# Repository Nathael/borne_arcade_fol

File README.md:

borne_arcade_fol
================

Borne Arcade pour la Fabrique d'Objets Libres

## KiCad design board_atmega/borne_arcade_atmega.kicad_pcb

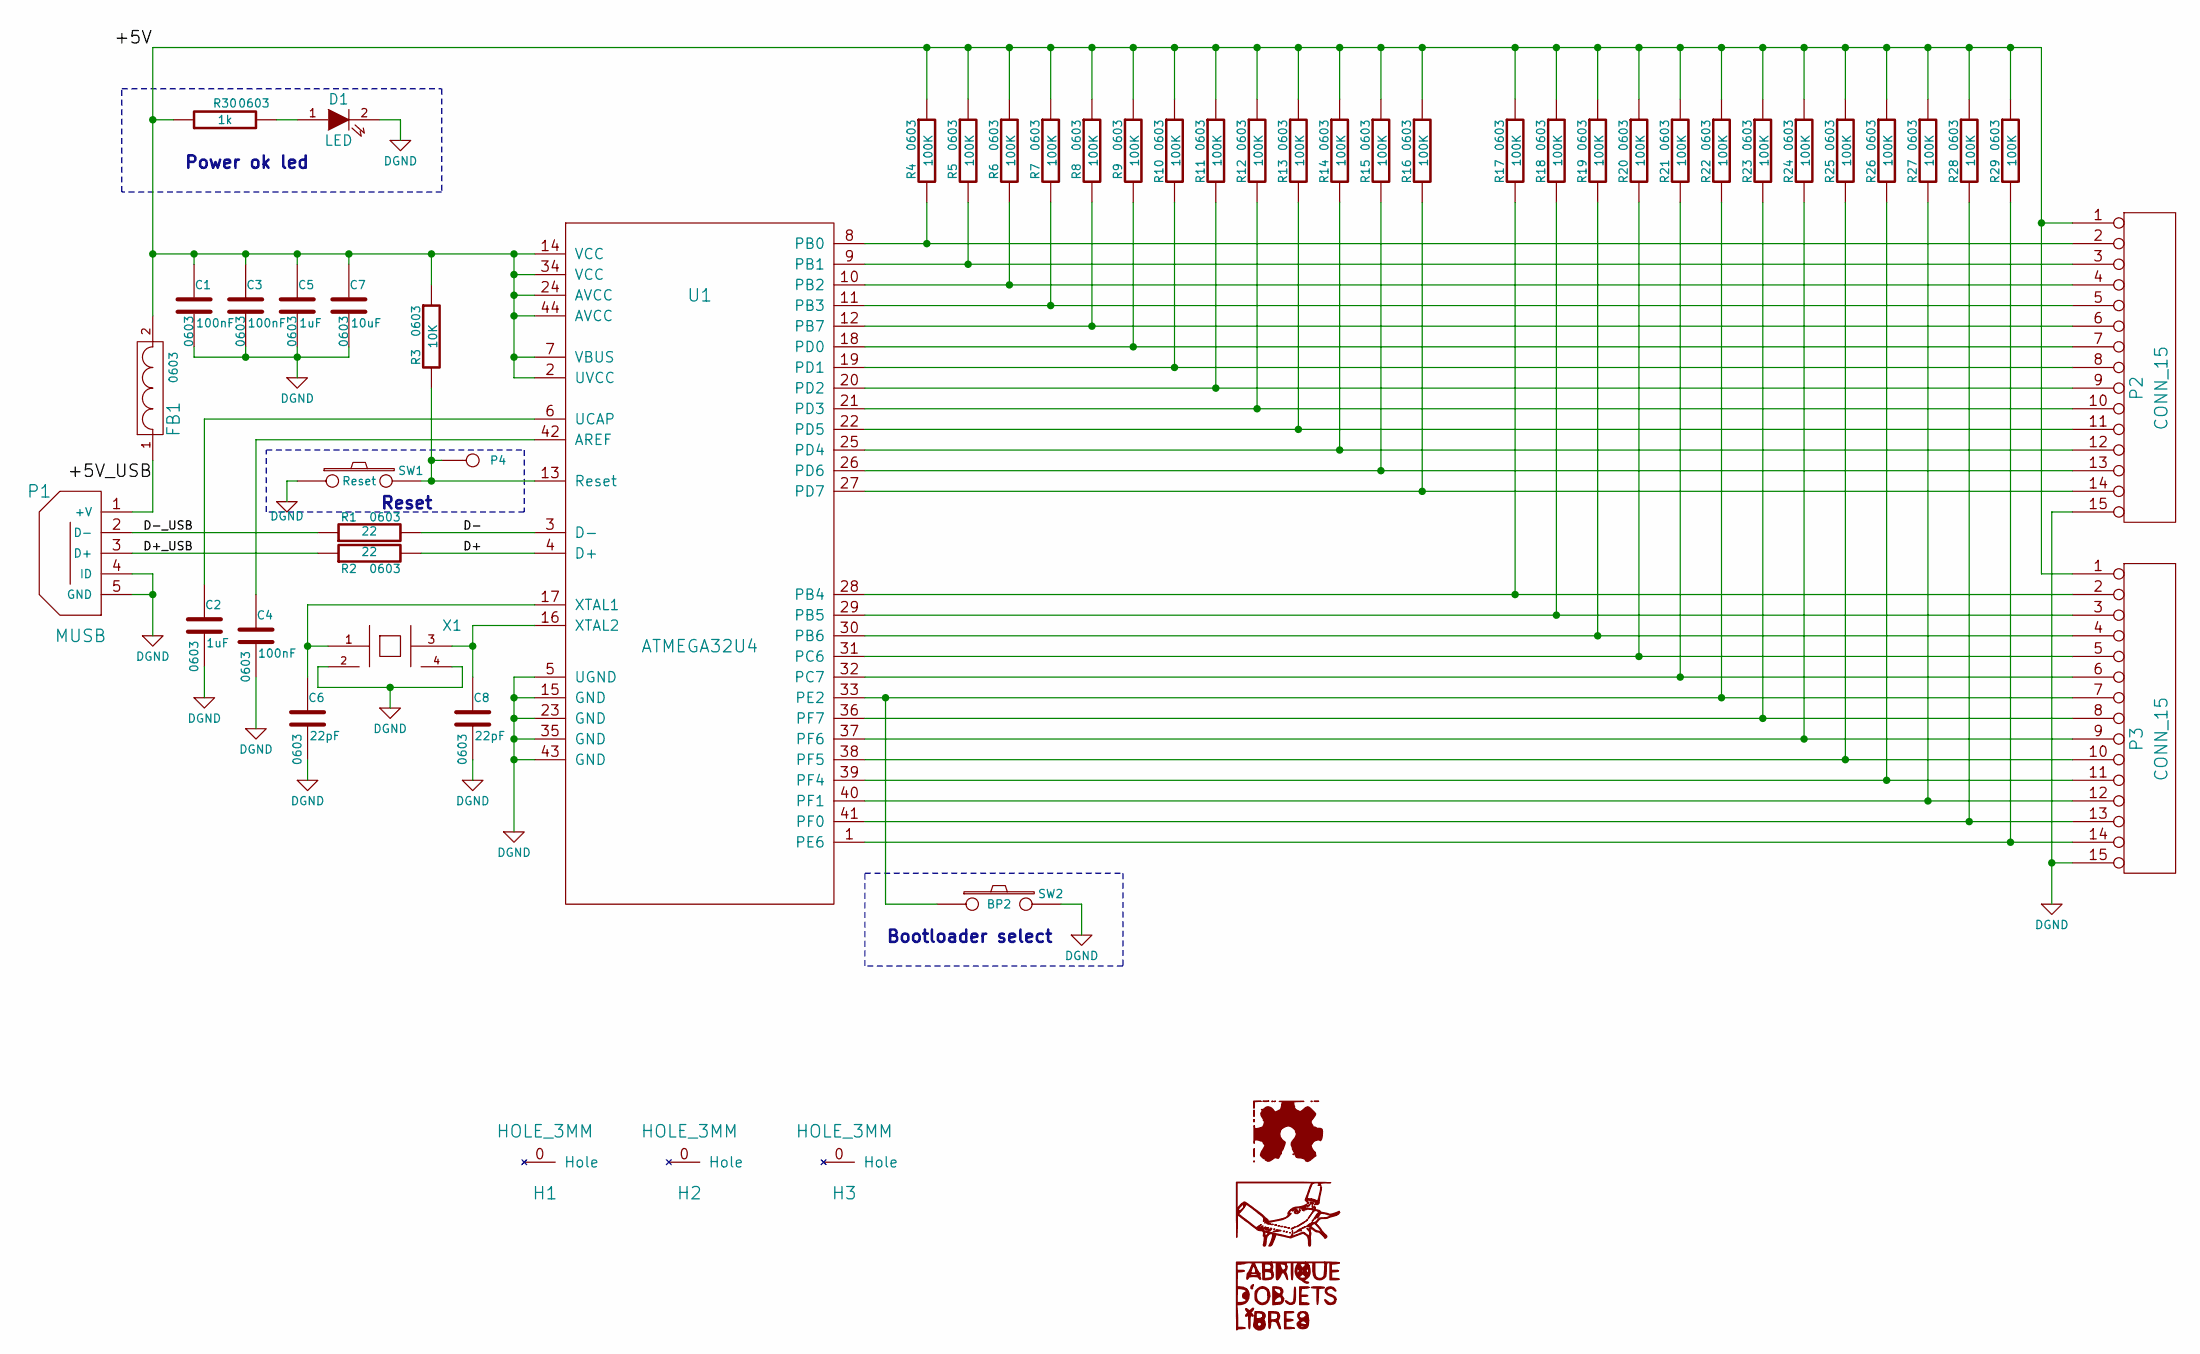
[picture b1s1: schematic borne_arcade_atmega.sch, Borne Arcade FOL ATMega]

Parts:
C1, C3, C4: 100nF; 0603
C2, C5: 1uF; 0603
C6, C8: 22pF; 0603
C7: 10uF; 0603
D1: LED
FB1: FILTER; 0603
G1: LOGO
G2: LOGO_FOL
G3: LOGO_OSHW
H1, H2, H3: HOLE_3MM
P1: MUSB
P2, P3: CONN_15
P4: CONN_1
R1, R2: 22; 0603
R3: 10K; 0603
R4, R5, R6, R7, R8, R9, R10, R11, R12, R13, R14, R15, R16, R17, R18, R19, R20, R21, R22, R23, R24, R25, R26, R27, R28, R29: 100K; 0603
R30: 1k; 0603
SW1: Reset
SW2: BP2
U1: ATMEGA32U4
X1: QUARTZ_CMS_4

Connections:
/+5V: C1.1, C3.1, C5.1, C7.1, FB1.2, P2.1, P3.1, R3.1, R4.1, R5.1, R6.1, R7.1, R8.1, R9.1, R10.1, R11.1, R12.1, R13.1, R14.1, R15.1, R16.1, R17.1, R18.1, R19.1, R20.1, R21.1, R22.1, R23.1, R24.1, R25.1, R26.1, R27.1, R28.1, R29.1, R30.1, U1.2 (UVCC), U1.7 (VBUS), U1.14 (VCC), U1.24 (AVCC), U1.34 (VCC), U1.44 (AVCC)
/+5V_USB: FB1.1, P1.1 (+V)
/D+: R2.2, U1.4 (D+)
/D+_USB: P1.3 (D+), R2.1
/D-: R1.2, U1.3 (D-)
/D-_USB: P1.2 (D-), R1.1
DGND: C1.2, C2.2, C3.2, C4.2, C5.2, C6.2, C7.2, C8.2, D1.2 (K), P1.4 (ID), P1.5 (GND), P2.15, P3.15, SW1.1, SW2.2, U1.5 (UGND), U1.15 (GND), U1.23 (GND), U1.35 (GND), U1.43 (GND), X1.2 (GND), X1.4 (GND)
unnamed: P2.9, R11.2, U1.20 (PD2)
unnamed: P2.8, R10.2, U1.19 (PD1)
unnamed: P2.7, R9.2, U1.18 (PD0)
unnamed: P2.6, R8.2, U1.12 (PB7)
unnamed: P2.5, R7.2, U1.11 (PB3)
unnamed: P2.4, R6.2, U1.10 (PB2)
unnamed: P2.3, R5.2, U1.9 (PB1)
unnamed: P2.2, R4.2, U1.8 (PB0)
unnamed: C2.1, U1.6 (UCAP)
unnamed: C8.1, U1.16 (XTAL2), X1.3
unnamed: P2.10, R12.2, U1.21 (PD3)
unnamed: P3.14, R29.2, U1.1 (PE6)
unnamed: D1.1 (A), R30.2
unnamed: P4.1, R3.2, SW1.2, U1.13 (Reset)
unnamed: P2.11, R13.2, U1.22 (PD5)
unnamed: P2.14, R16.2, U1.27 (PD7)
unnamed: P2.13, R15.2, U1.26 (PD6)
unnamed: P2.12, R14.2, U1.25 (PD4)
unnamed: P3.7, R22.2, SW2.1, U1.33 (PE2)
unnamed: P3.13, R28.2, U1.41 (PF0)
unnamed: P3.12, R27.2, U1.40 (PF1)
unnamed: P3.11, R26.2, U1.39 (PF4)
unnamed: P3.10, R25.2, U1.38 (PF5)
unnamed: P3.9, R24.2, U1.37 (PF6)
unnamed: P3.8, R23.2, U1.36 (PF7)
unnamed: P3.6, R21.2, U1.32 (PC7)
unnamed: P3.5, R20.2, U1.31 (PC6)
unnamed: P3.4, R19.2, U1.30 (PB6)
unnamed: P3.3, R18.2, U1.29 (PB5)
unnamed: P3.2, R17.2, U1.28 (PB4)
unnamed: C4.1, U1.42 (AREF)
unnamed: C6.1, U1.17 (XTAL1), X1.1

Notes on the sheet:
Power ok led
Bootloader select
Reset

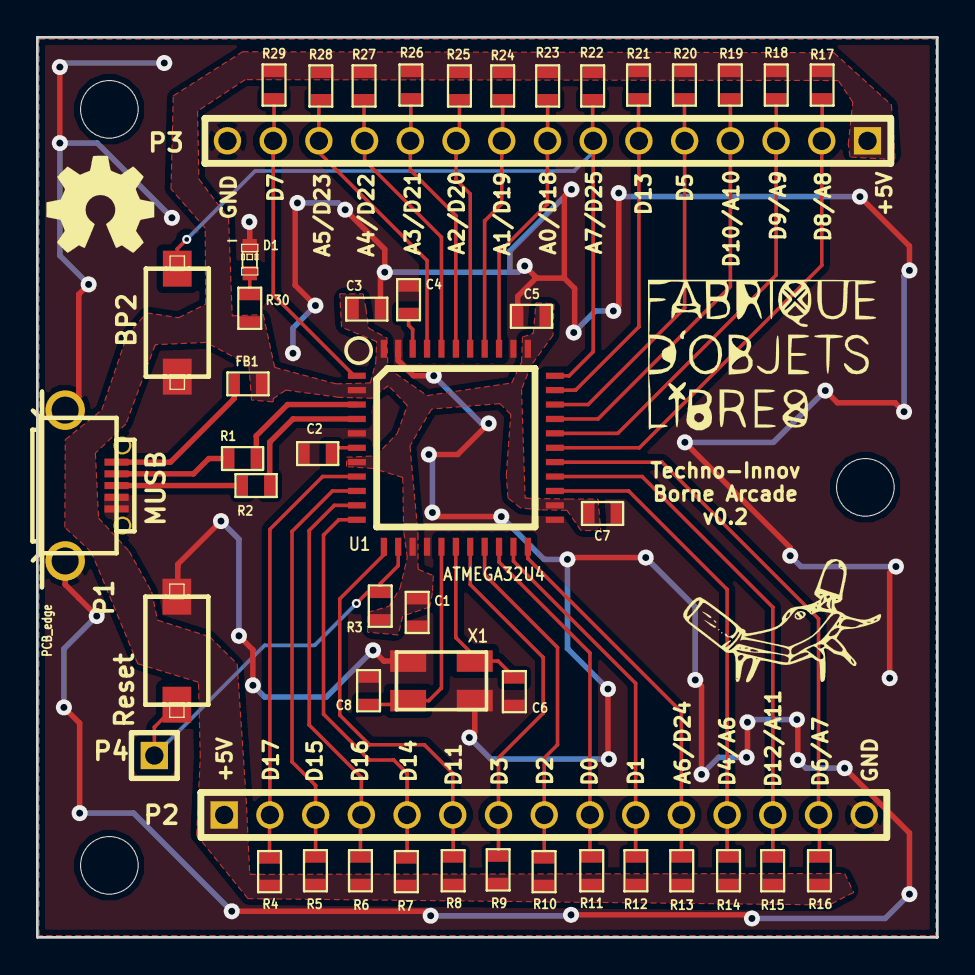
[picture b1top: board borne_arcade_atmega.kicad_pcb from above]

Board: 2 copper layers, 50.0 x 50.0 mm, 54 parts (0 on the bottom side), 39 nets.

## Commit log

2014-07-08 Rename README file as README !
2014-07-08 Add kicad generated files to ignore list, and update for C compilation objects
2014-07-08 Base library comming from Techno-Innov's kicad library
2014-07-08 First draft of board, using ATMega32U4.
2014-07-08 Ajout des logos de la fabrique d'objets libres
2014-07-08 Adding page information (licence, version, author) Adding logos
2014-07-08 Adding footprints for 7b quartz and mini USB connector
2014-07-08 Allowing different parts to be under different licenses (mainly boards under CC-By-SA)
2014-07-08 Last missing footprint
2014-07-08 Layout and some modifications to ease layout
2014-07-17 First version produced
2014-11-10 Nev revision v0.2 : - Adding the switches for reset and ISP mode selection - Addind reset pin - Changed USB connector to micro-USB (was mini-USB) - Adding power led - Using "arduino" names on top sil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
2014-11-10 Adding BOM, with farnell refs.

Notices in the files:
board_atmega/borne_arcade_atmega.kicad_pcb:
Licence : CC-By-SA
